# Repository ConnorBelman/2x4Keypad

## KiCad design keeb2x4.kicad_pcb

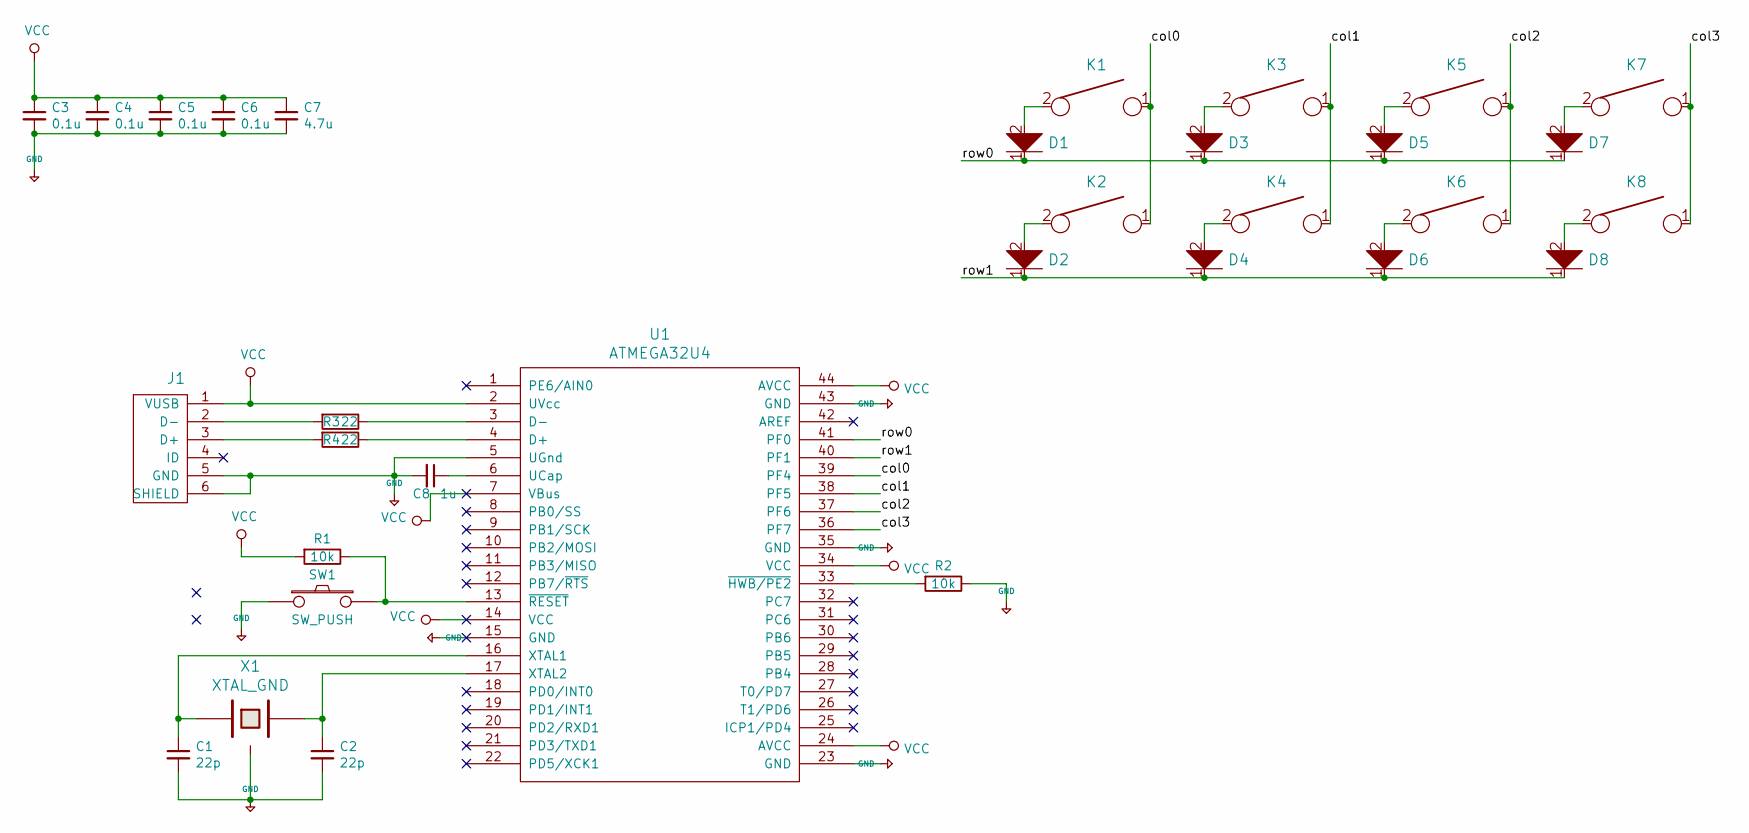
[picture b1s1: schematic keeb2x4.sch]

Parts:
C1, C2: 22p; C_0805_2012Metric_Pad1.15x1.40mm_HandSolder
C3, C4, C5, C6: 0.1u; C_0805_2012Metric_Pad1.15x1.40mm_HandSolder
C7: 4.7u; C_0805_2012Metric_Pad1.15x1.40mm_HandSolder
C8: 1u; C_0805_2012Metric_Pad1.15x1.40mm_HandSolder
D1, D2, D3, D4, D5, D6, D7, D8: D; D_SOD123_axial
J1: USB_mini_micro_B; USB_miniB_hirose_5S8
K1, K2, K3, K4, K5, K6, K7, K8: KEYSW; Mx_Alps_100
R1, R2: 10k; R_0805_2012Metric_Pad1.15x1.40mm_HandSolder
R3, R4: 22; R_0805_2012Metric_Pad1.15x1.40mm_HandSolder
SW1: SW_PUSH; SW_SPST_TL3342
U1: ATMEGA32U4; TQFP-44_10x10mm_P0.8mm
X1: XTAL_GND; crystal_FA238-TSX3225

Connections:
+5V: C1.2, C2.2, C3.2, C4.2, C5.2, C6.2, C7.2, C8.2, J1.5 (GND), J1.6 (SHIELD), R2.1, SW1.1, U1.5 (UGnd), U1.15 (GND), U1.23 (GND), U1.35 (GND), U1.43 (GND), X1.3
/col0: K1.1, K2.1, U1.39 (PF4)
/col1: K3.1, K4.1, U1.38 (PF5)
/col2: K5.1, K6.1, U1.37 (PF6)
/col3: K7.1, K8.1, U1.36 (PF7)
/row0: D1.1, D3.1, D5.1, D7.1, U1.41 (PF0)
/row1: D2.1, D4.1, D6.1, D8.1, U1.40 (PF1)
unnamed: C1.1, U1.16 (XTAL1), X1.1
unnamed: C2.1, U1.17 (XTAL2), X1.2
unnamed: C8.1, U1.6 (UCap)
unnamed: D1.2, K1.2
unnamed: D2.2, K2.2
unnamed: D3.2, K3.2
unnamed: D4.2, K4.2
unnamed: D5.2, K5.2
unnamed: D6.2, K6.2
unnamed: D7.2, K7.2
unnamed: D8.2, K8.2
unnamed: J1.2 (D-), R3.2
unnamed: J1.3 (D+), R4.2
unnamed: R1.1, SW1.2, U1.13 (~RESET)
unnamed: R2.2, U1.33 (~HWB/PE2)
unnamed: R3.1, U1.3 (D-)
unnamed: R4.1, U1.4 (D+)
VCC: C3.1, C4.1, C5.1, C6.1, C7.1, J1.1 (VUSB), R1.2, U1.2 (UVcc), U1.7 (VBus), U1.14 (VCC), U1.24 (AVCC), U1.34 (VCC), U1.44 (AVCC)

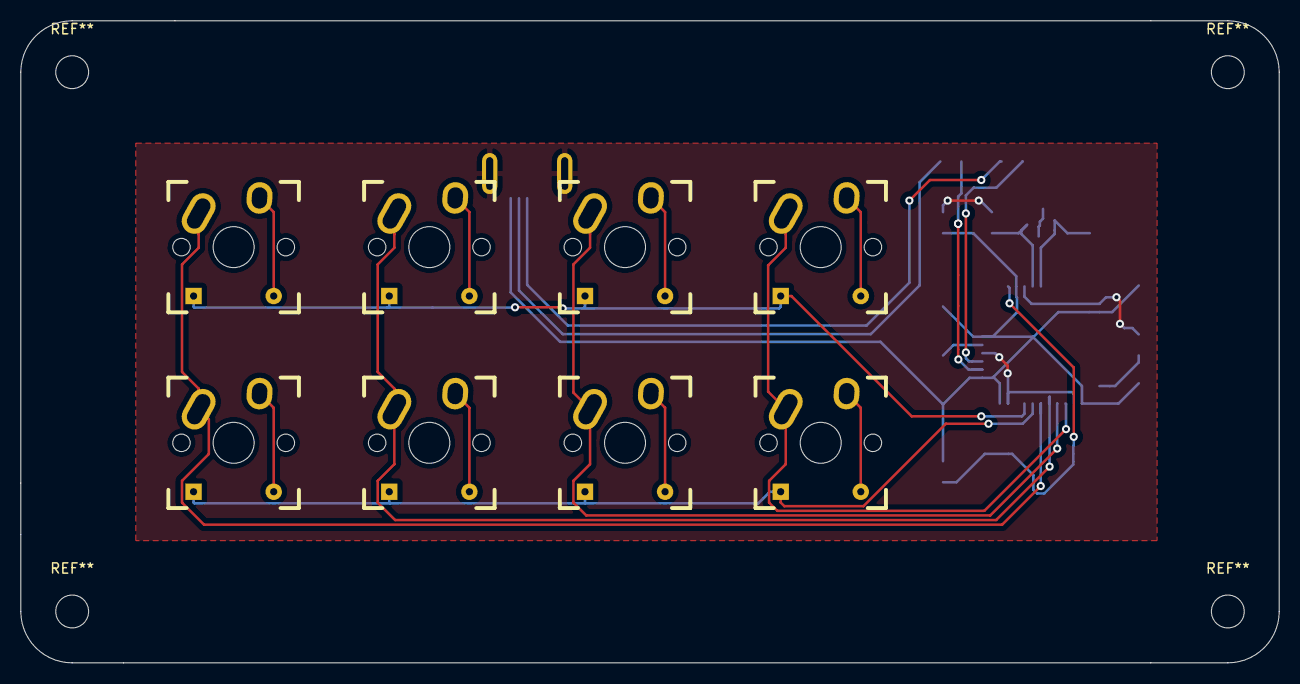
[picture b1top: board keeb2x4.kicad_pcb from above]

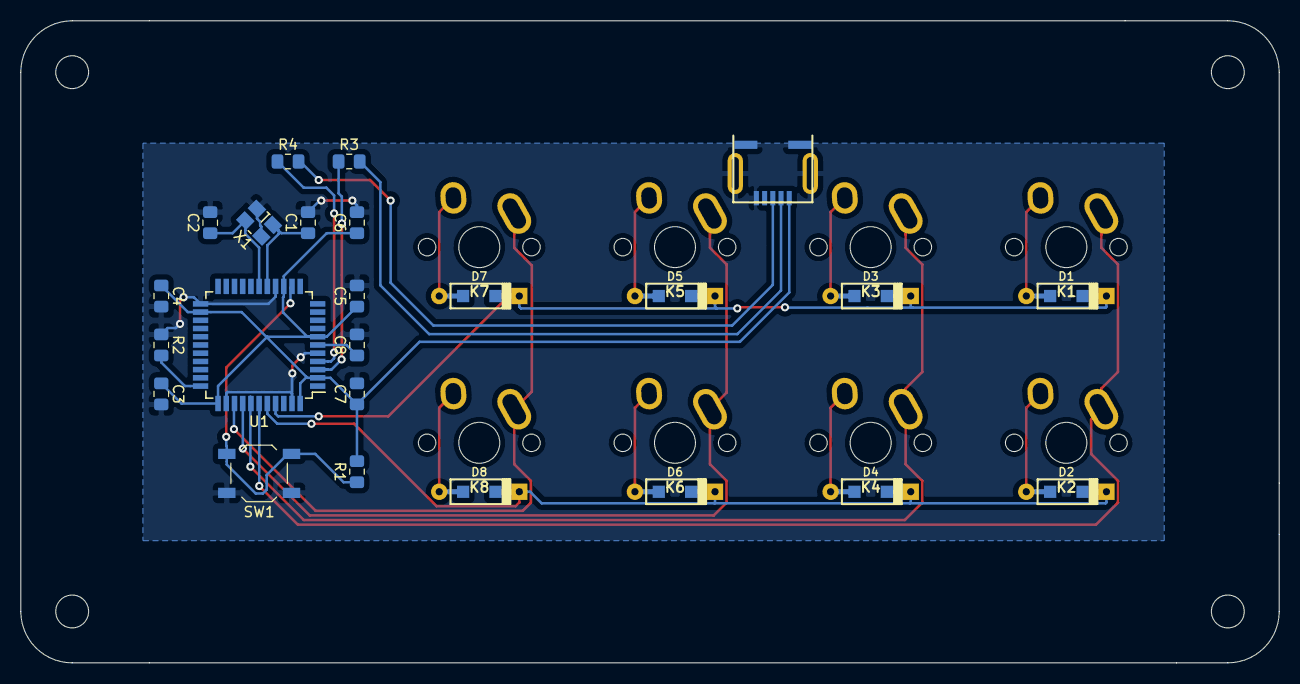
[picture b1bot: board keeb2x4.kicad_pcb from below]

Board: 2 copper layers, 122.5 x 62.5 mm, 32 parts (24 on the bottom side), 25 nets.

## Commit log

2019-03-20 added gerber
2019-03-21 Updated pcb dimensions
2019-03-21 added case files
